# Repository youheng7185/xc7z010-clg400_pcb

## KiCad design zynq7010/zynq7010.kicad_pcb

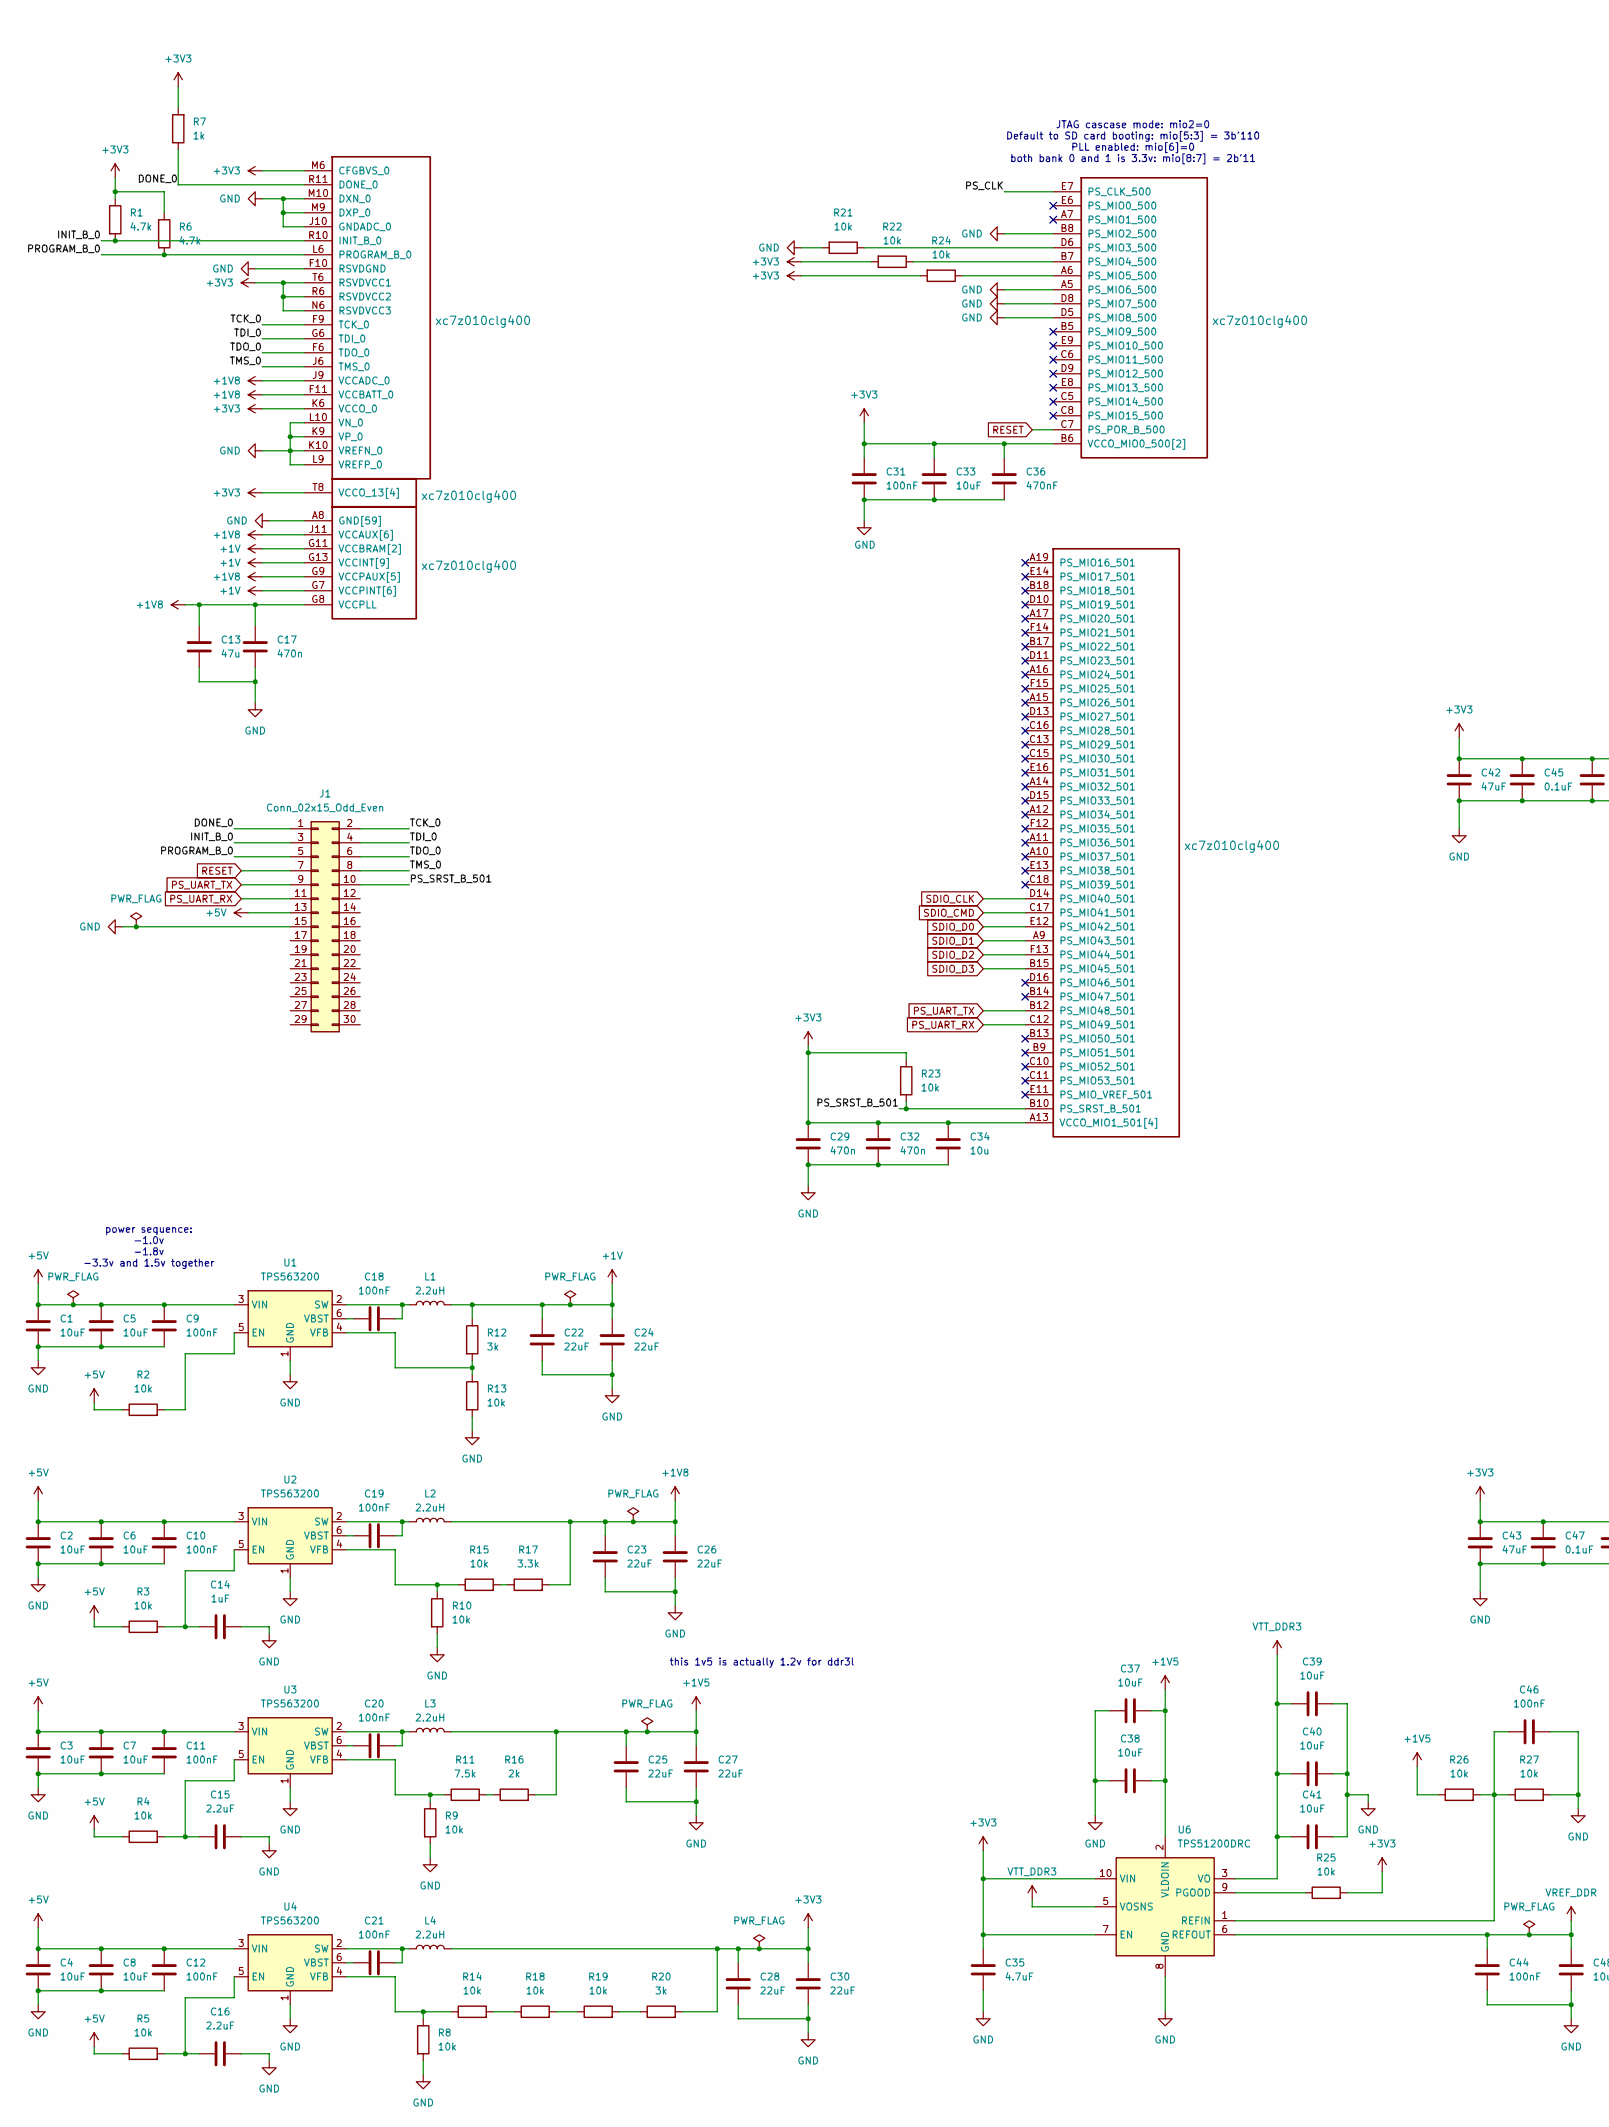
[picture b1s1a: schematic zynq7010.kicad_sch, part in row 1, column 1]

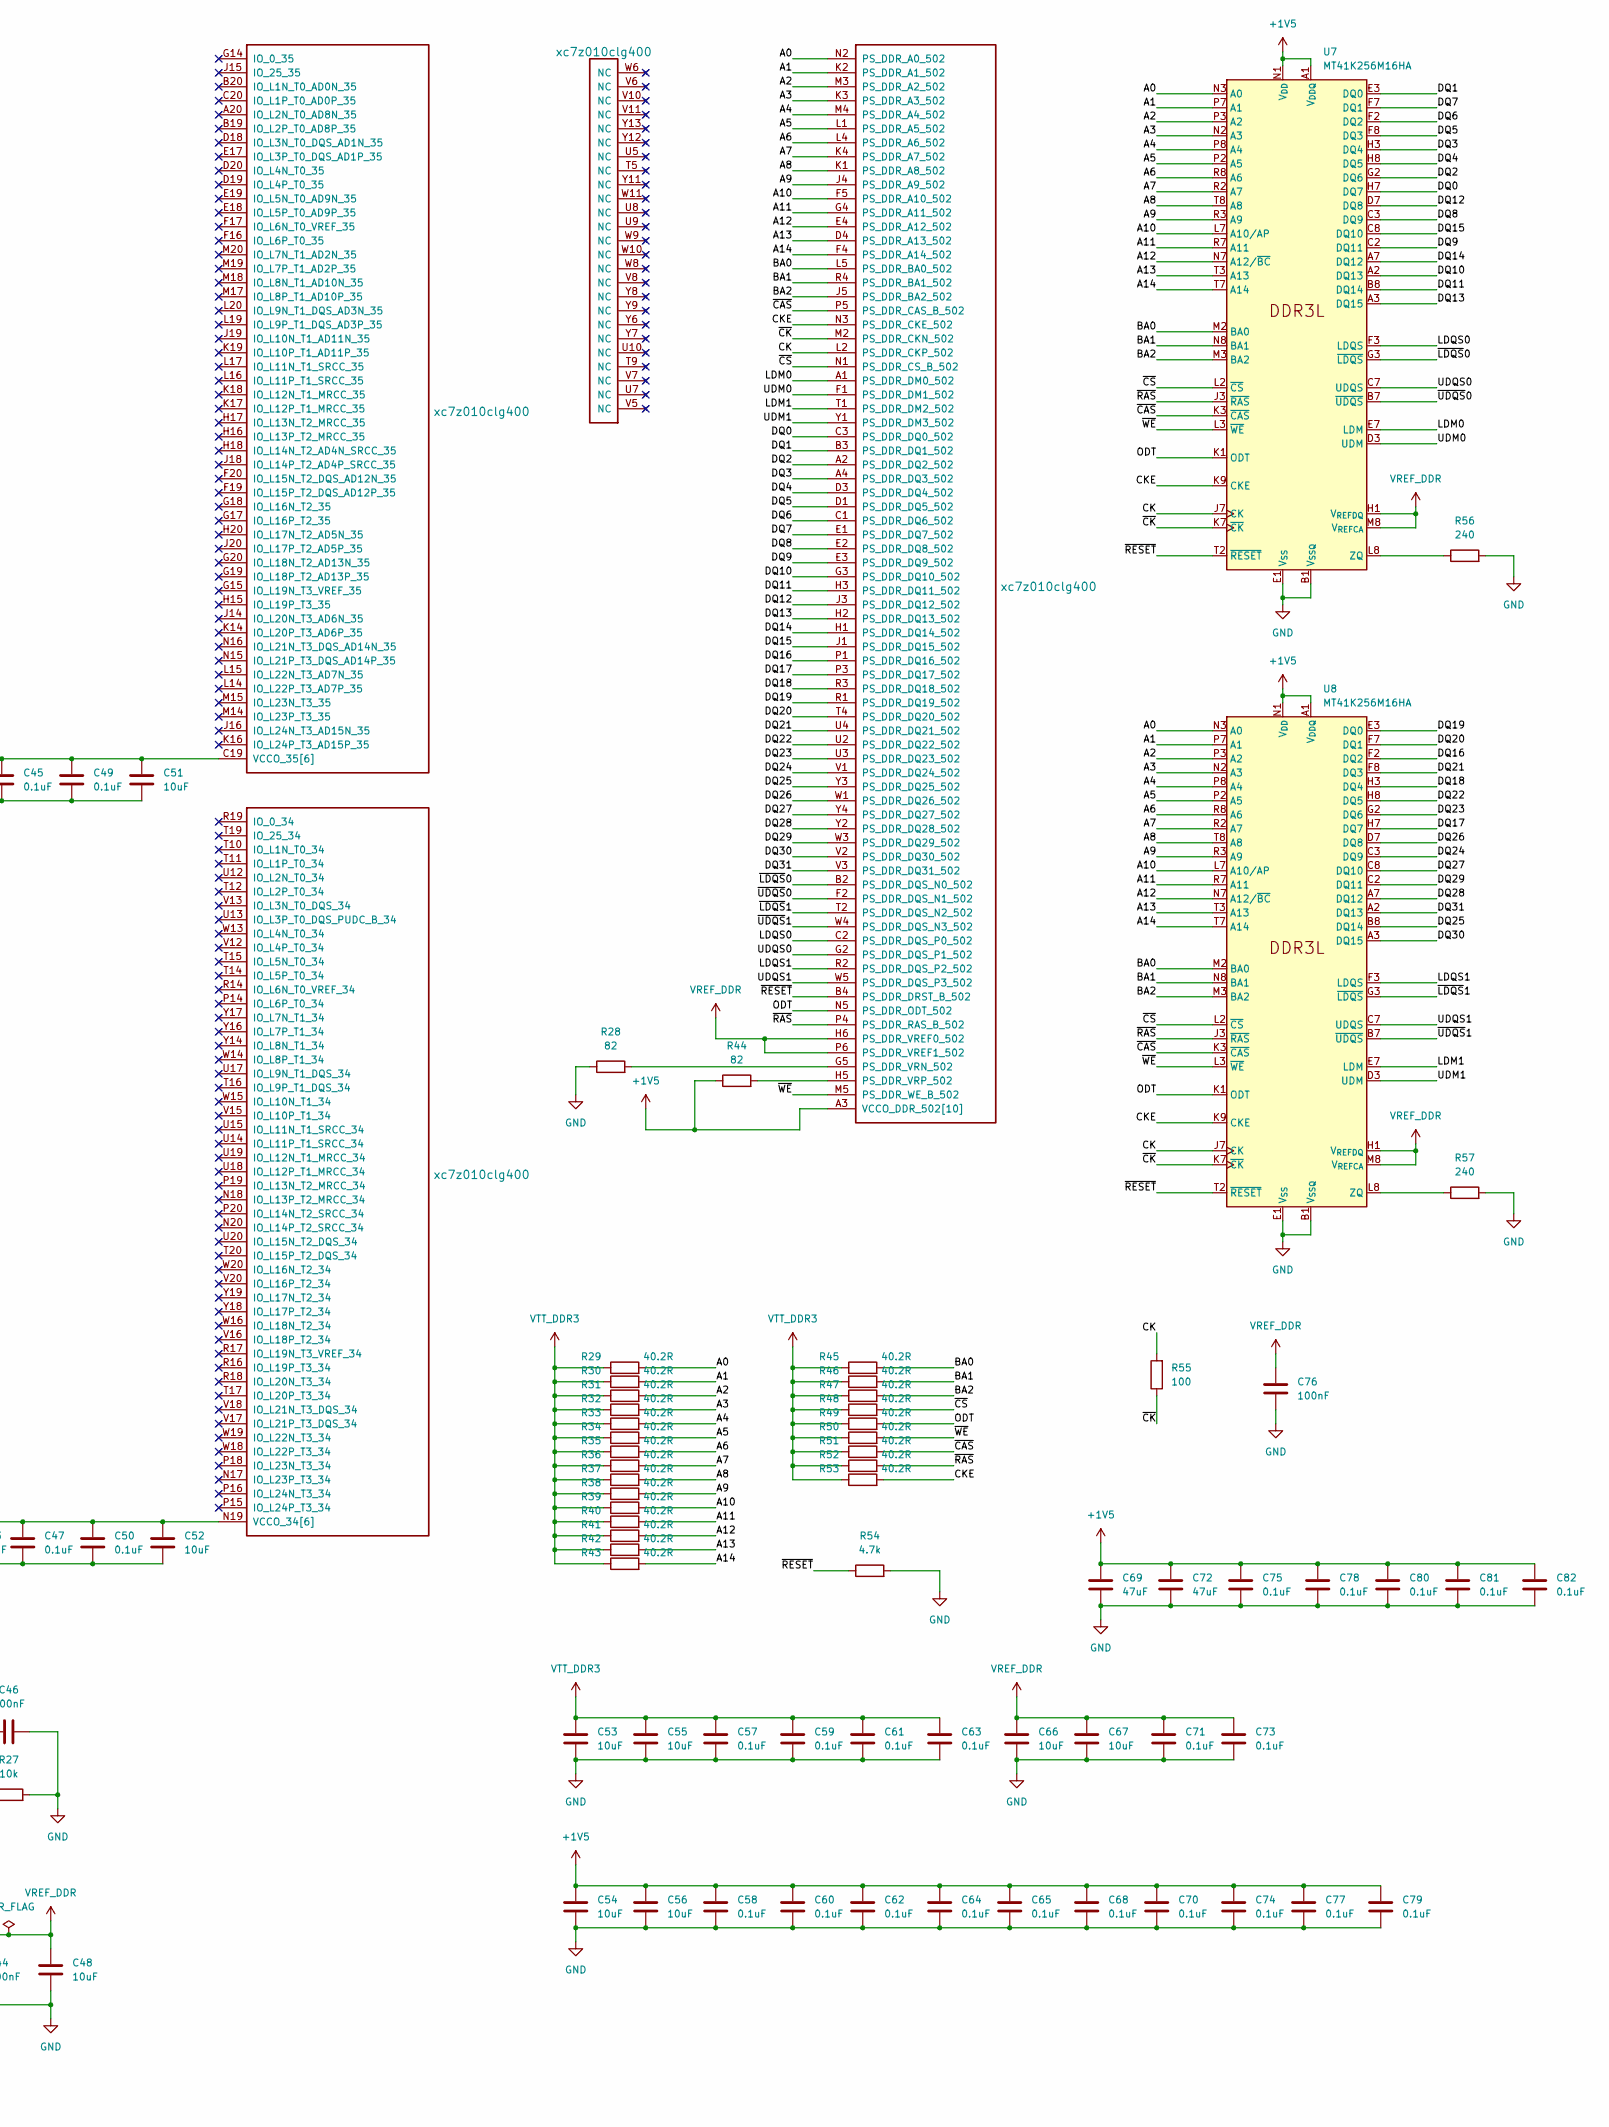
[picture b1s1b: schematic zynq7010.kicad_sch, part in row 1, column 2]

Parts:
C1, C2, C3, C4, C5, C6, C7, C8: 10uF; C_0603_1608Metric
C9, C10, C11, C12, C18, C19, C20, C21, C31, C44, C46, C76: 100nF; C_0402_1005Metric
C13: 47u; C_0402_1005Metric
C14: 1uF; C_0402_1005Metric
C15, C16: 2.2uF; C_0402_1005Metric
C17, C29, C32: 470n; C_0402_1005Metric
C22, C23, C24, C25, C26, C27, C28, C30: 22uF; C_0603_1608Metric
C33, C37, C38, C39, C40, C41, C48, C51, C52, C53, C54, C55, C56, C66, C67: 10uF; C_0402_1005Metric
C34: 10u; C_0402_1005Metric
C35: 4.7uF; C_0402_1005Metric
C36: 470nF; C_0402_1005Metric
C42, C43, C69, C72: 47uF; C_0402_1005Metric
C45, C47, C49, C50, C57, C58, C59, C60, C61, C62, C63, C64, C65, C68, C70, C71, C73, C74, C75, C77, C78, C79, C80, C81, C82: 0.1uF; C_0402_1005Metric
J1: Conn_02x15_Odd_Even; PinHeader_2x15_P2.54mm_Vertical
L1, L2, L3, L4: 2.2uH; L_Sunlord_SWPA252012S
R1, R6, R54: 4.7k; R_0402_1005Metric
R2, R3, R4, R5, R8, R9, R10, R13, R14, R15, R18, R19, R21, R22, R23, R24, R25, R26, R27: 10k; R_0402_1005Metric
R7: 1k; R_0402_1005Metric
R11: 7.5k; R_0402_1005Metric
R12, R20: 3k; R_0402_1005Metric
R16: 2k; R_0402_1005Metric
R17: 3.3k; R_0402_1005Metric
R28, R44: 82; R_0402_1005Metric
R29, R30, R31, R32, R33, R34, R35, R36, R37, R38, R39, R40, R41, R42, R43, R45, R46, R47, R48, R49, R50, R51, R52, R53: 40.2R; R_0402_1005Metric
R55: 100; R_0402_1005Metric
R56, R57: 240; R_0402_1005Metric
U1, U2, U3, U4: TPS563200; SOT-23-6
U5: xc7z010clg400; Xilinx_CLG400_NoPaste_JLC_Package_Delay
U6: TPS51200DRC; VSON-10-1EP_3x3mm_P0.5mm_EP1.65x2.4mm
U7, U8: MT41K256M16HA; Micron_FBGA-96_9x14mm_Layout9x16_P0.8mm

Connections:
+1V: C22.1, C24.1, L1.2, R12.1, U5.G7 (VCCPINT[6]), U5.G11 (VCCBRAM[2]), U5.G13 (VCCINT[9]), U5.H10 (VCCBRAM[2]), U5.H12 (VCCINT[9]), U5.J7 (VCCPINT[6]), U5.J13 (VCCINT[9]), U5.K12 (VCCINT[9]), U5.L7 (VCCPINT[6]), U5.L13 (VCCINT[9]), U5.M12 (VCCINT[9]), U5.N7 (VCCPINT[6]), U5.N13 (VCCINT[9]), U5.P8 (VCCPINT[6]), U5.P12 (VCCINT[9]), U5.R7 (VCCPINT[6]), U5.R13 (VCCINT[9])
+1V5: C25.1, C27.1, C37.2, C38.2, C54.1, C56.1, C58.1, C60.1, C62.1, C64.1, C65.1, C68.1, C69.1, C70.1, C72.1, C74.1, C75.1, C77.1, C78.1, C79.1, C80.1, C81.1, C82.1, L3.2, R16.2, R26.1, R44.1, U5.A3 (VCCO_DDR_502[10]), U5.D2 (VCCO_DDR_502[10]), U5.E5 (VCCO_DDR_502[10]), U5.G1 (VCCO_DDR_502[10]), U5.H4 (VCCO_DDR_502[10]), U5.L3 (VCCO_DDR_502[10]), U5.P2 (VCCO_DDR_502[10]), U5.R5 (VCCO_DDR_502[10]), U5.U1 (VCCO_DDR_502[10]), U5.V4 (VCCO_DDR_502[10]), U6.2 (VLDOIN), U7.A1 (V_{DDQ}), U7.A8 (V_{DDQ}), U7.B2 (V_{DD}), U7.C1 (V_{DDQ}), U7.C9 (V_{DDQ}), U7.D2 (V_{DDQ}), U7.D9 (V_{DD}), U7.E9 (V_{DDQ}), U7.F1 (V_{DDQ}), U7.G7 (V_{DD}), U7.H2 (V_{DDQ}), U7.H9 (V_{DDQ}), U7.K2 (V_{DD}), U7.K8 (V_{DD}), U7.N1 (V_{DD}), U7.N9 (V_{DD}), U7.R1 (V_{DD}), U7.R9 (V_{DD}), U8.A1 (V_{DDQ}), U8.A8 (V_{DDQ}), U8.B2 (V_{DD}), U8.C1 (V_{DDQ}), U8.C9 (V_{DDQ}), U8.D2 (V_{DDQ}), U8.D9 (V_{DD}), U8.E9 (V_{DDQ}), U8.F1 (V_{DDQ}), U8.G7 (V_{DD}), U8.H2 (V_{DDQ}), U8.H9 (V_{DDQ}), U8.K2 (V_{DD}), U8.K8 (V_{DD}), U8.N1 (V_{DD}), U8.N9 (V_{DD}), U8.R1 (V_{DD}), U8.R9 (V_{DD})
+1V8: C13.1, C17.1, C23.1, C26.1, L2.2, R17.2, U5.F8 (VCCPAUX[5]), U5.F11 (VCCBATT_0), U5.G8 (VCCPLL), U5.G9 (VCCPAUX[5]), U5.H8 (VCCPAUX[5]), U5.J9 (VCCADC_0), U5.J11 (VCCAUX[6]), U5.K8 (VCCPAUX[5]), U5.L11 (VCCAUX[6]), U5.M8 (VCCPAUX[5]), U5.N9 (VCCAUX[6]), U5.N11 (VCCAUX[6]), U5.P10 (VCCAUX[6]), U5.R9 (VCCAUX[6])
+3V3: C28.1, C29.1, C30.1, C31.1, C32.1, C33.1, C34.1, C35.1, C36.1, C42.2, C43.2, C45.2, C47.2, C49.2, C50.2, C51.2, C52.2, L4.2, R1.1, R6.1, R7.2, R20.2, R22.2, R23.1, R24.2, R25.2, U5.A13 (VCCO_MIO1_501[4]), U5.B6 (VCCO_MIO0_500[2]), U5.B16 (VCCO_MIO1_501[4]), U5.C19 (VCCO_35[6]), U5.D7 (VCCO_MIO0_500[2]), U5.D12 (VCCO_MIO1_501[4]), U5.E15 (VCCO_MIO1_501[4]), U5.F18 (VCCO_35[6]), U5.H14 (VCCO_35[6]), U5.J17 (VCCO_35[6]), U5.K6 (VCCO_0), U5.K20 (VCCO_35[6]), U5.M6 (CFGBVS_0), U5.M16 (VCCO_35[6]), U5.N6 (RSVDVCC3), U5.N19 (VCCO_34[6]), U5.R6 (RSVDVCC2), U5.R15 (VCCO_34[6]), U5.T6 (RSVDVCC1), U5.T8 (VCCO_13[4]), U5.T18 (VCCO_34[6]), U5.U11 (VCCO_13[4]), U5.V14 (VCCO_34[6]), U5.W7 (VCCO_13[4]), U5.W17 (VCCO_34[6]), U5.Y10 (VCCO_13[4]), U5.Y20 (VCCO_34[6]), U6.7 (EN), U6.10 (VIN)
+5V: C1.1, C2.1, C3.1, C4.1, C5.1, C6.1, C7.1, C8.1, C9.1, C10.1, C11.1, C12.1, J1.13, R2.1, R3.1, R4.1, R5.1, U1.3 (VIN), U2.3 (VIN), U3.3 (VIN), U4.3 (VIN)
/A0: R29.2, U5.N2 (PS_DDR_A0_502), U7.N3 (A0), U8.N3 (A0)
/A1: R30.2, U5.K2 (PS_DDR_A1_502), U7.P7 (A1), U8.P7 (A1)
/A2: R31.2, U5.M3 (PS_DDR_A2_502), U7.P3 (A2), U8.P3 (A2)
/A3: R32.2, U5.K3 (PS_DDR_A3_502), U7.N2 (A3), U8.N2 (A3)
/A4: R33.2, U5.M4 (PS_DDR_A4_502), U7.P8 (A4), U8.P8 (A4)
/A5: R34.2, U5.L1 (PS_DDR_A5_502), U7.P2 (A5), U8.P2 (A5)
/A6: R35.2, U5.L4 (PS_DDR_A6_502), U7.R8 (A6), U8.R8 (A6)
/A7: R36.2, U5.K4 (PS_DDR_A7_502), U7.R2 (A7), U8.R2 (A7)
/A8: R37.2, U5.K1 (PS_DDR_A8_502), U7.T8 (A8), U8.T8 (A8)
/A9: R38.2, U5.J4 (PS_DDR_A9_502), U7.R3 (A9), U8.R3 (A9)
/A10: R39.2, U5.F5 (PS_DDR_A10_502), U7.L7 (A10/AP), U8.L7 (A10/AP)
/A11: R40.2, U5.G4 (PS_DDR_A11_502), U7.R7 (A11), U8.R7 (A11)
/A12: R41.2, U5.E4 (PS_DDR_A12_502), U7.N7 (A12/~BC), U8.N7 (A12/~BC)
/A13: R42.2, U5.D4 (PS_DDR_A13_502), U7.T3 (A13), U8.T3 (A13)
/A14: R43.2, U5.F4 (PS_DDR_A14_502), U7.T7 (A14), U8.T7 (A14)
/BA0: R45.2, U5.L5 (PS_DDR_BA0_502), U7.M2 (BA0), U8.M2 (BA0)
/BA1: R46.2, U5.R4 (PS_DDR_BA1_502), U7.N8 (BA1), U8.N8 (BA1)
/BA2: R47.2, U5.J5 (PS_DDR_BA2_502), U7.M3 (BA2), U8.M3 (BA2)
/CK: R55.2, U5.L2 (PS_DDR_CKP_502), U7.J7 (CK), U8.J7 (CK)
/CKE: R53.2, U5.N3 (PS_DDR_CKE_502), U7.K9 (CKE), U8.K9 (CKE)
/DONE_0: J1.1, R7.1, U5.R11 (DONE_0)
/DQ0: U5.C3 (PS_DDR_DQ0_502), U7.H7 (DQ7)
/DQ1: U5.B3 (PS_DDR_DQ1_502), U7.E3 (DQ0)
/DQ2: U5.A2 (PS_DDR_DQ2_502), U7.G2 (DQ6)
/DQ3: U5.A4 (PS_DDR_DQ3_502), U7.H3 (DQ4)
/DQ4: U5.D3 (PS_DDR_DQ4_502), U7.H8 (DQ5)
/DQ5: U5.D1 (PS_DDR_DQ5_502), U7.F8 (DQ3)
/DQ6: U5.C1 (PS_DDR_DQ6_502), U7.F2 (DQ2)
/DQ7: U5.E1 (PS_DDR_DQ7_502), U7.F7 (DQ1)
/DQ8: U5.E2 (PS_DDR_DQ8_502), U7.C3 (DQ9)
/DQ9: U5.E3 (PS_DDR_DQ9_502), U7.C2 (DQ11)
/DQ10: U5.G3 (PS_DDR_DQ10_502), U7.A2 (DQ13)
/DQ11: U5.H3 (PS_DDR_DQ11_502), U7.B8 (DQ14)
/DQ12: U5.J3 (PS_DDR_DQ12_502), U7.D7 (DQ8)
/DQ13: U5.H2 (PS_DDR_DQ13_502), U7.A3 (DQ15)
/DQ14: U5.H1 (PS_DDR_DQ14_502), U7.A7 (DQ12)
/DQ15: U5.J1 (PS_DDR_DQ15_502), U7.C8 (DQ10)
/DQ16: U5.P1 (PS_DDR_DQ16_502), U8.F2 (DQ2)
/DQ17: U5.P3 (PS_DDR_DQ17_502), U8.H7 (DQ7)
/DQ18: U5.R3 (PS_DDR_DQ18_502), U8.H3 (DQ4)
/DQ19: U5.R1 (PS_DDR_DQ19_502), U8.E3 (DQ0)
/DQ20: U5.T4 (PS_DDR_DQ20_502), U8.F7 (DQ1)
/DQ21: U5.U4 (PS_DDR_DQ21_502), U8.F8 (DQ3)
/DQ22: U5.U2 (PS_DDR_DQ22_502), U8.H8 (DQ5)
/DQ23: U5.U3 (PS_DDR_DQ23_502), U8.G2 (DQ6)
/DQ24: U5.V1 (PS_DDR_DQ24_502), U8.C3 (DQ9)
/DQ25: U5.Y3 (PS_DDR_DQ25_502), U8.B8 (DQ14)
/DQ26: U5.W1 (PS_DDR_DQ26_502), U8.D7 (DQ8)
/DQ27: U5.Y4 (PS_DDR_DQ27_502), U8.C8 (DQ10)
/DQ28: U5.Y2 (PS_DDR_DQ28_502), U8.A7 (DQ12)
/DQ29: U5.W3 (PS_DDR_DQ29_502), U8.C2 (DQ11)
/DQ30: U5.V2 (PS_DDR_DQ30_502), U8.A3 (DQ15)
/DQ31: U5.V3 (PS_DDR_DQ31_502), U8.A2 (DQ13)
/INIT_B_0: J1.3, R1.2, U5.R10 (INIT_B_0)
/LDM0: U5.A1 (PS_DDR_DM0_502), U7.E7 (LDM)
/LDM1: U5.T1 (PS_DDR_DM2_502), U8.E7 (LDM)
/LDQS0: U5.C2 (PS_DDR_DQS_P0_502), U7.F3 (LDQS)
/LDQS1: U5.R2 (PS_DDR_DQS_P2_502), U8.F3 (LDQS)
/ODT: R49.2, U5.N5 (PS_DDR_ODT_502), U7.K1 (ODT), U8.K1 (ODT)
/PROGRAM_B_0: J1.5, R6.2, U5.L6 (PROGRAM_B_0)
/PS_CLK: U5.E7 (PS_CLK_500)
/PS_SRST_B_501: J1.10, R23.2, U5.B10 (PS_SRST_B_501)
/TCK_0: J1.2, U5.F9 (TCK_0)
/TDI_0: J1.4, U5.G6 (TDI_0)
/TDO_0: J1.6, U5.F6 (TDO_0)
/TMS_0: J1.8, U5.J6 (TMS_0)
/UDM0: U5.F1 (PS_DDR_DM1_502), U7.D3 (UDM)
/UDM1: U5.Y1 (PS_DDR_DM3_502), U8.D3 (UDM)
/UDQS0: U5.G2 (PS_DDR_DQS_P1_502), U7.C7 (UDQS)
/UDQS1: U5.W5 (PS_DDR_DQS_P3_502), U8.C7 (UDQS)
/~CAS: R51.2, U5.P5 (PS_DDR_CAS_B_502), U7.K3 (~CAS), U8.K3 (~CAS)
/~CK: R55.1, U5.M2 (PS_DDR_CKN_502), U7.K7 (~CK), U8.K7 (~CK)
/~CS: R48.2, U5.N1 (PS_DDR_CS_B_502), U7.L2 (~CS), U8.L2 (~CS)
/~LDQS0: U5.B2 (PS_DDR_DQS_N0_502), U7.G3 (~LDQS)
/~LDQS1: U5.T2 (PS_DDR_DQS_N2_502), U8.G3 (~LDQS)
/~RAS: R52.2, U5.P4 (PS_DDR_RAS_B_502), U7.J3 (~RAS), U8.J3 (~RAS)
/~RESET: R54.1, U5.B4 (PS_DDR_DRST_B_502), U7.T2 (~RESET), U8.T2 (~RESET)
/~UDQS0: U5.F2 (PS_DDR_DQS_N1_502), U7.B7 (~UDQS)
/~UDQS1: U5.W4 (PS_DDR_DQS_N3_502), U8.B7 (~UDQS)
/~WE: R50.2, U5.M5 (PS_DDR_WE_B_502), U7.L3 (~WE), U8.L3 (~WE)
GND: C1.2, C2.2, C3.2, C4.2, C5.2, C6.2, C7.2, C8.2, C9.2, C10.2, C11.2, C12.2, C13.2, C14.2, C15.2, C16.2, C17.2, C22.2, C23.2, C24.2, C25.2, C26.2, C27.2, C28.2, C29.2, C30.2, C31.2, C32.2, C33.2, C34.2, C35.2, C36.2, C37.1, C38.1, C39.2, C40.2, C41.2, C42.1, C43.1, C44.2, C45.1, C46.2, C47.1, C48.2, C49.1, C50.1, C51.1, C52.1, C53.2, C54.2, C55.2, C56.2, C57.2, C58.2, C59.2, C60.2, C61.2, C62.2, C63.2, C64.2, C65.2, C66.2, C67.2, C68.2, C69.2, C70.2, C71.2, C72.2, C73.2, C74.2, C75.2, C76.2, C77.2, C78.2, C79.2, C80.2, C81.2, C82.2, J1.15, R8.2, R9.2, R10.2, R13.2, R21.2, R27.2, R28.1, R54.2, R56.2, R57.2, U1.1 (GND), U2.1 (GND), U3.1 (GND), U4.1 (GND), U5.A5 (PS_MIO6_500), U5.A8 (GND[59]), U5.A18 (GND[59]), U5.B1 (GND[59]), U5.B8 (PS_MIO2_500), U5.B11 (GND[59]), U5.C4 (GND[59]), U5.C9 (GND[59]), U5.C14 (GND[59]), U5.D5 (PS_MIO8_500), U5.D8 (PS_MIO7_500), U5.D17 (GND[59]), U5.E10 (GND[59]), U5.E20 (GND[59]), U5.F3 (GND[59]), U5.F7 (GND[59]), U5.F10 (RSVDGND), U5.G10 (GND[59]), U5.G12 (GND[59]), U5.G16 (GND[59]), U5.H7 (GND[59]), U5.H9 (GND[59]), U5.H11 (GND[59]), U5.H13 (GND[59]), U5.H19 (GND[59]), U5.J2 (GND[59]), U5.J8 (GND[59]), U5.J10 (GNDADC_0), U5.J12 (GND[59]), U5.K5 (GND[59]), U5.K7 (GND[59]), U5.K9 (VP_0), U5.K10 (VREFN_0), U5.K11 (GND[59]), U5.K13 (GND[59]), U5.K15 (GND[59]), U5.L8 (GND[59]), U5.L9 (VREFP_0), U5.L10 (VN_0), U5.L12 (GND[59]), U5.L18 (GND[59]), U5.M1 (GND[59]), U5.M7 (GND[59]), U5.M9 (DXP_0), U5.M10 (DXN_0), U5.M11 (GND[59]), U5.M13 (GND[59]), U5.N4 (GND[59]), U5.N8 (GND[59]), U5.N10 (GND[59]), U5.N12 (GND[59]), U5.N14 (GND[59]), U5.P7 (GND[59]), U5.P9 (GND[59]), U5.P11 (GND[59]), U5.P13 (GND[59]), U5.P17 (GND[59]), U5.R8 (GND[59]), U5.R12 (GND[59]), U5.R20 (GND[59]), U5.T3 (GND[59]), U5.T7 (GND[59]), U5.T13 (GND[59]), U5.U6 (GND[59]), U5.U16 (GND[59]), U5.V9 (GND[59]), U5.V19 (GND[59]), U5.W2 (GND[59]), U5.W12 (GND[59]), U5.Y5 (GND[59]), U5.Y15 (GND[59]), U6.4 (GND), U6.8 (GND), U6.11 (GND), U7.A9 (V_{SS}), U7.B1 (V_{SSQ}), U7.B3 (V_{SS}), U7.B9 (V_{SSQ}), U7.D1 (V_{SSQ}), U7.D8 (V_{SSQ}), U7.E1 (V_{SS}), U7.E2 (V_{SSQ}), U7.E8 (V_{SSQ}), U7.F9 (V_{SSQ}), U7.G1 (V_{SSQ}), U7.G8 (V_{SS}), U7.G9 (V_{SSQ}), U7.J2 (V_{SS}), U7.J8 (V_{SS}), U7.M1 (V_{SS}), U7.M9 (V_{SS}), U7.P1 (V_{SS}), U7.P9 (V_{SS}), U7.T1 (V_{SS}), U7.T9 (V_{SS}), U8.A9 (V_{SS}), U8.B1 (V_{SSQ}), U8.B3 (V_{SS}), U8.B9 (V_{SSQ}), U8.D1 (V_{SSQ}), U8.D8 (V_{SSQ}), U8.E1 (V_{SS}), U8.E2 (V_{SSQ}), U8.E8 (V_{SSQ}), U8.F9 (V_{SSQ}), U8.G1 (V_{SSQ}), U8.G8 (V_{SS}), U8.G9 (V_{SSQ}), U8.J2 (V_{SS}), U8.J8 (V_{SS}), U8.M1 (V_{SS}), U8.M9 (V_{SS}), U8.P1 (V_{SS}), U8.P9 (V_{SS}), U8.T1 (V_{SS}), U8.T9 (V_{SS})
unnamed: R11.2, R16.1
unnamed: R14.2, R18.1
unnamed: R15.2, R17.1
unnamed: R18.2, R19.1
unnamed: R19.2, R20.1
unnamed: R2.2, U1.5 (EN)
unnamed: C18.2, L1.1, U1.2 (SW)
unnamed: C18.1, U1.6 (VBST)
unnamed: R12.2, R13.1, U1.4 (VFB)
unnamed: C14.1, R3.2, U2.5 (EN)
unnamed: C19.2, L2.1, U2.2 (SW)
unnamed: C19.1, U2.6 (VBST)
unnamed: R10.1, R15.1, U2.4 (VFB)
unnamed: C15.1, R4.2, U3.5 (EN)
unnamed: C20.2, L3.1, U3.2 (SW)
unnamed: C20.1, U3.6 (VBST)
unnamed: R9.1, R11.1, U3.4 (VFB)
unnamed: C16.1, R5.2, U4.5 (EN)
unnamed: C21.2, L4.1, U4.2 (SW)
unnamed: C21.1, U4.6 (VBST)
unnamed: R8.1, R14.1, U4.4 (VFB)
unnamed: R21.1, U5.D6 (PS_MIO3_500)
unnamed: R22.1, U5.B7 (PS_MIO4_500)
unnamed: R24.1, U5.A6 (PS_MIO5_500)
unnamed: R28.2, U5.G5 (PS_DDR_VRN_502)
unnamed: R44.2, U5.H5 (PS_DDR_VRP_502)
unnamed: R25.1, U6.9 (PGOOD)
unnamed: C46.1, R26.2, R27.1, U6.1 (REFIN)
unnamed: R56.1, U7.L8 (ZQ)
unnamed: R57.1, U8.L8 (ZQ)
PS_UART_RX: J1.11, U5.C12 (PS_MIO49_501)
PS_UART_TX: J1.9, U5.B12 (PS_MIO48_501)
RESET: J1.7, U5.C7 (PS_POR_B_500)
SDIO_CLK: U5.D14 (PS_MIO40_501)
SDIO_CMD: U5.C17 (PS_MIO41_501)
SDIO_D0: U5.E12 (PS_MIO42_501)
SDIO_D1: U5.A9 (PS_MIO43_501)
SDIO_D2: U5.F13 (PS_MIO44_501)
SDIO_D3: U5.B15 (PS_MIO45_501)
VREF_DDR: C44.1, C48.1, C66.1, C67.1, C71.1, C73.1, C76.1, U5.H6 (PS_DDR_VREF0_502), U5.P6 (PS_DDR_VREF1_502), U6.6 (REFOUT), U7.H1 (V_{REFDQ}), U7.M8 (V_{REFCA}), U8.H1 (V_{REFDQ}), U8.M8 (V_{REFCA})
VTT_DDR3: C39.1, C40.1, C41.1, C53.1, C55.1, C57.1, C59.1, C61.1, C63.1, R29.1, R30.1, R31.1, R32.1, R33.1, R34.1, R35.1, R36.1, R37.1, R38.1, R39.1, R40.1, R41.1, R42.1, R43.1, R45.1, R46.1, R47.1, R48.1, R49.1, R50.1, R51.1, R52.1, R53.1, U6.3 (VO), U6.5 (VOSNS)

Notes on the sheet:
JTAG cascase mode: mio2=0 Default to SD card booting: mio[5:3] = 3b'110 PLL enabled: mio[6]=0 both bank 0 and 1 is 3.3v: mio[8:7] = 2b'11
this 1v5 is actually 1.2v for ddr3l
power sequence: -1.0v -1.8v -3.3v and 1.5v together

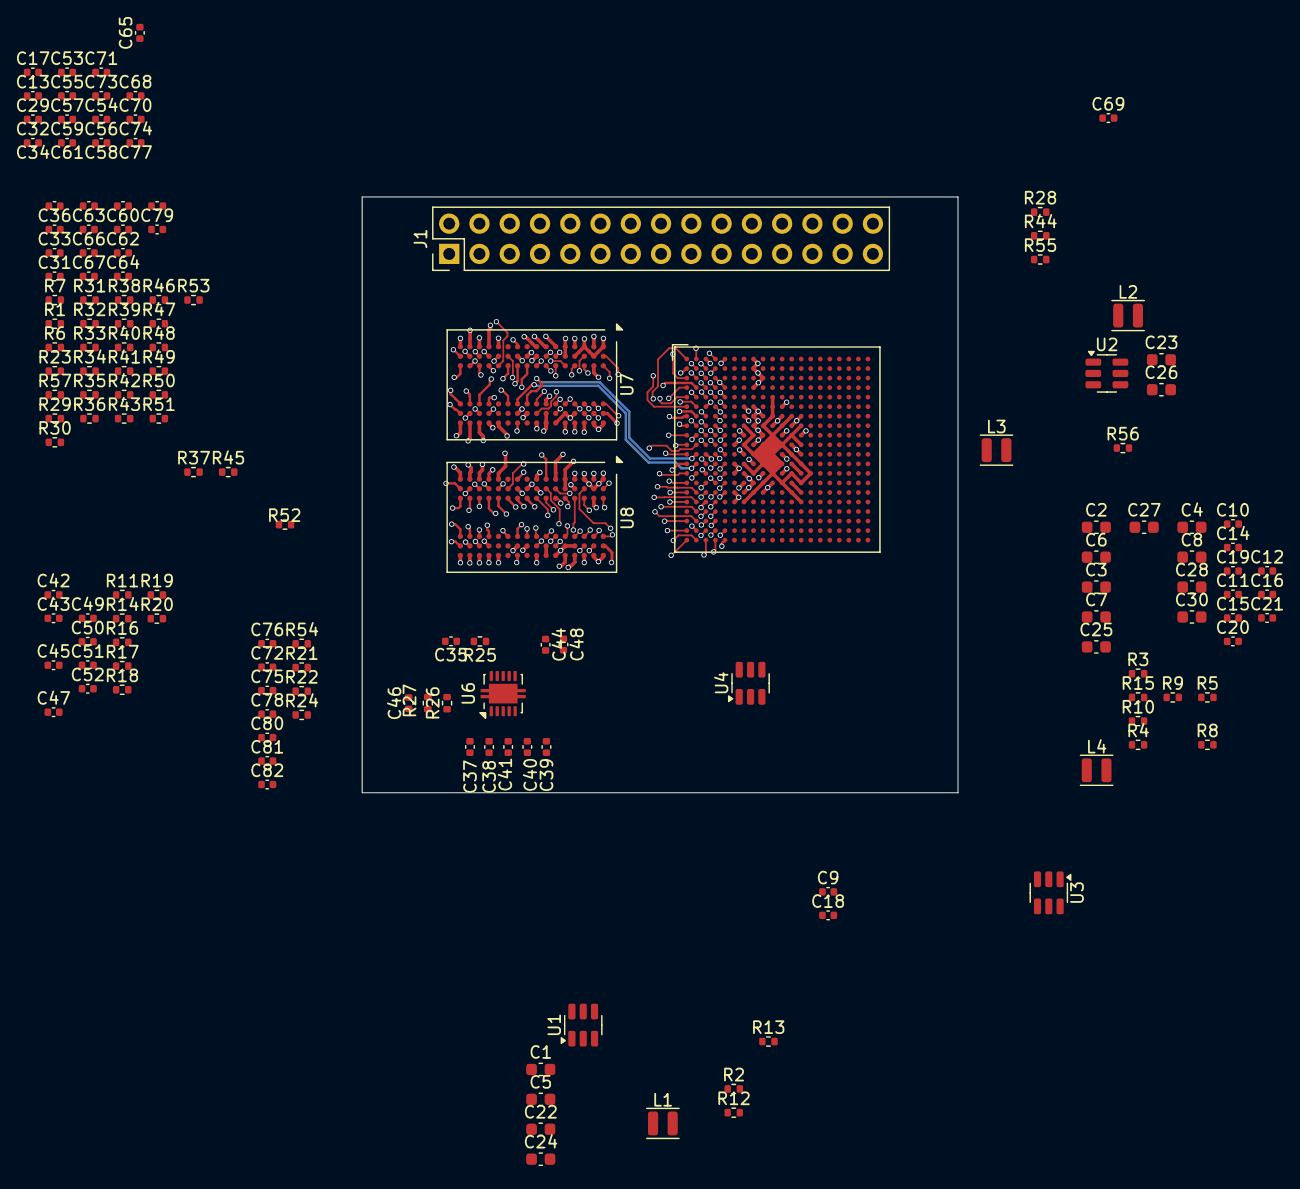
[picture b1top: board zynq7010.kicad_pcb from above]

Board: 8 copper layers, 50.0 x 50.0 mm, 152 parts (0 on the bottom side), 120 nets.

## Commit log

2025-09-04 done basic schematics
2025-09-04 finish dcdc and vtt sch, later do crystal and sd card
2025-09-05 done routing between two ddr3
2025-09-07 done routing between zynq and two ddr3, not gonna do length matching
